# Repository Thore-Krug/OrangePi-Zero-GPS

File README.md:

# OrangePi-Zero-GPS
Addon Board for the OrangePi Zero Featuring a L80-R GPS Module

## Render

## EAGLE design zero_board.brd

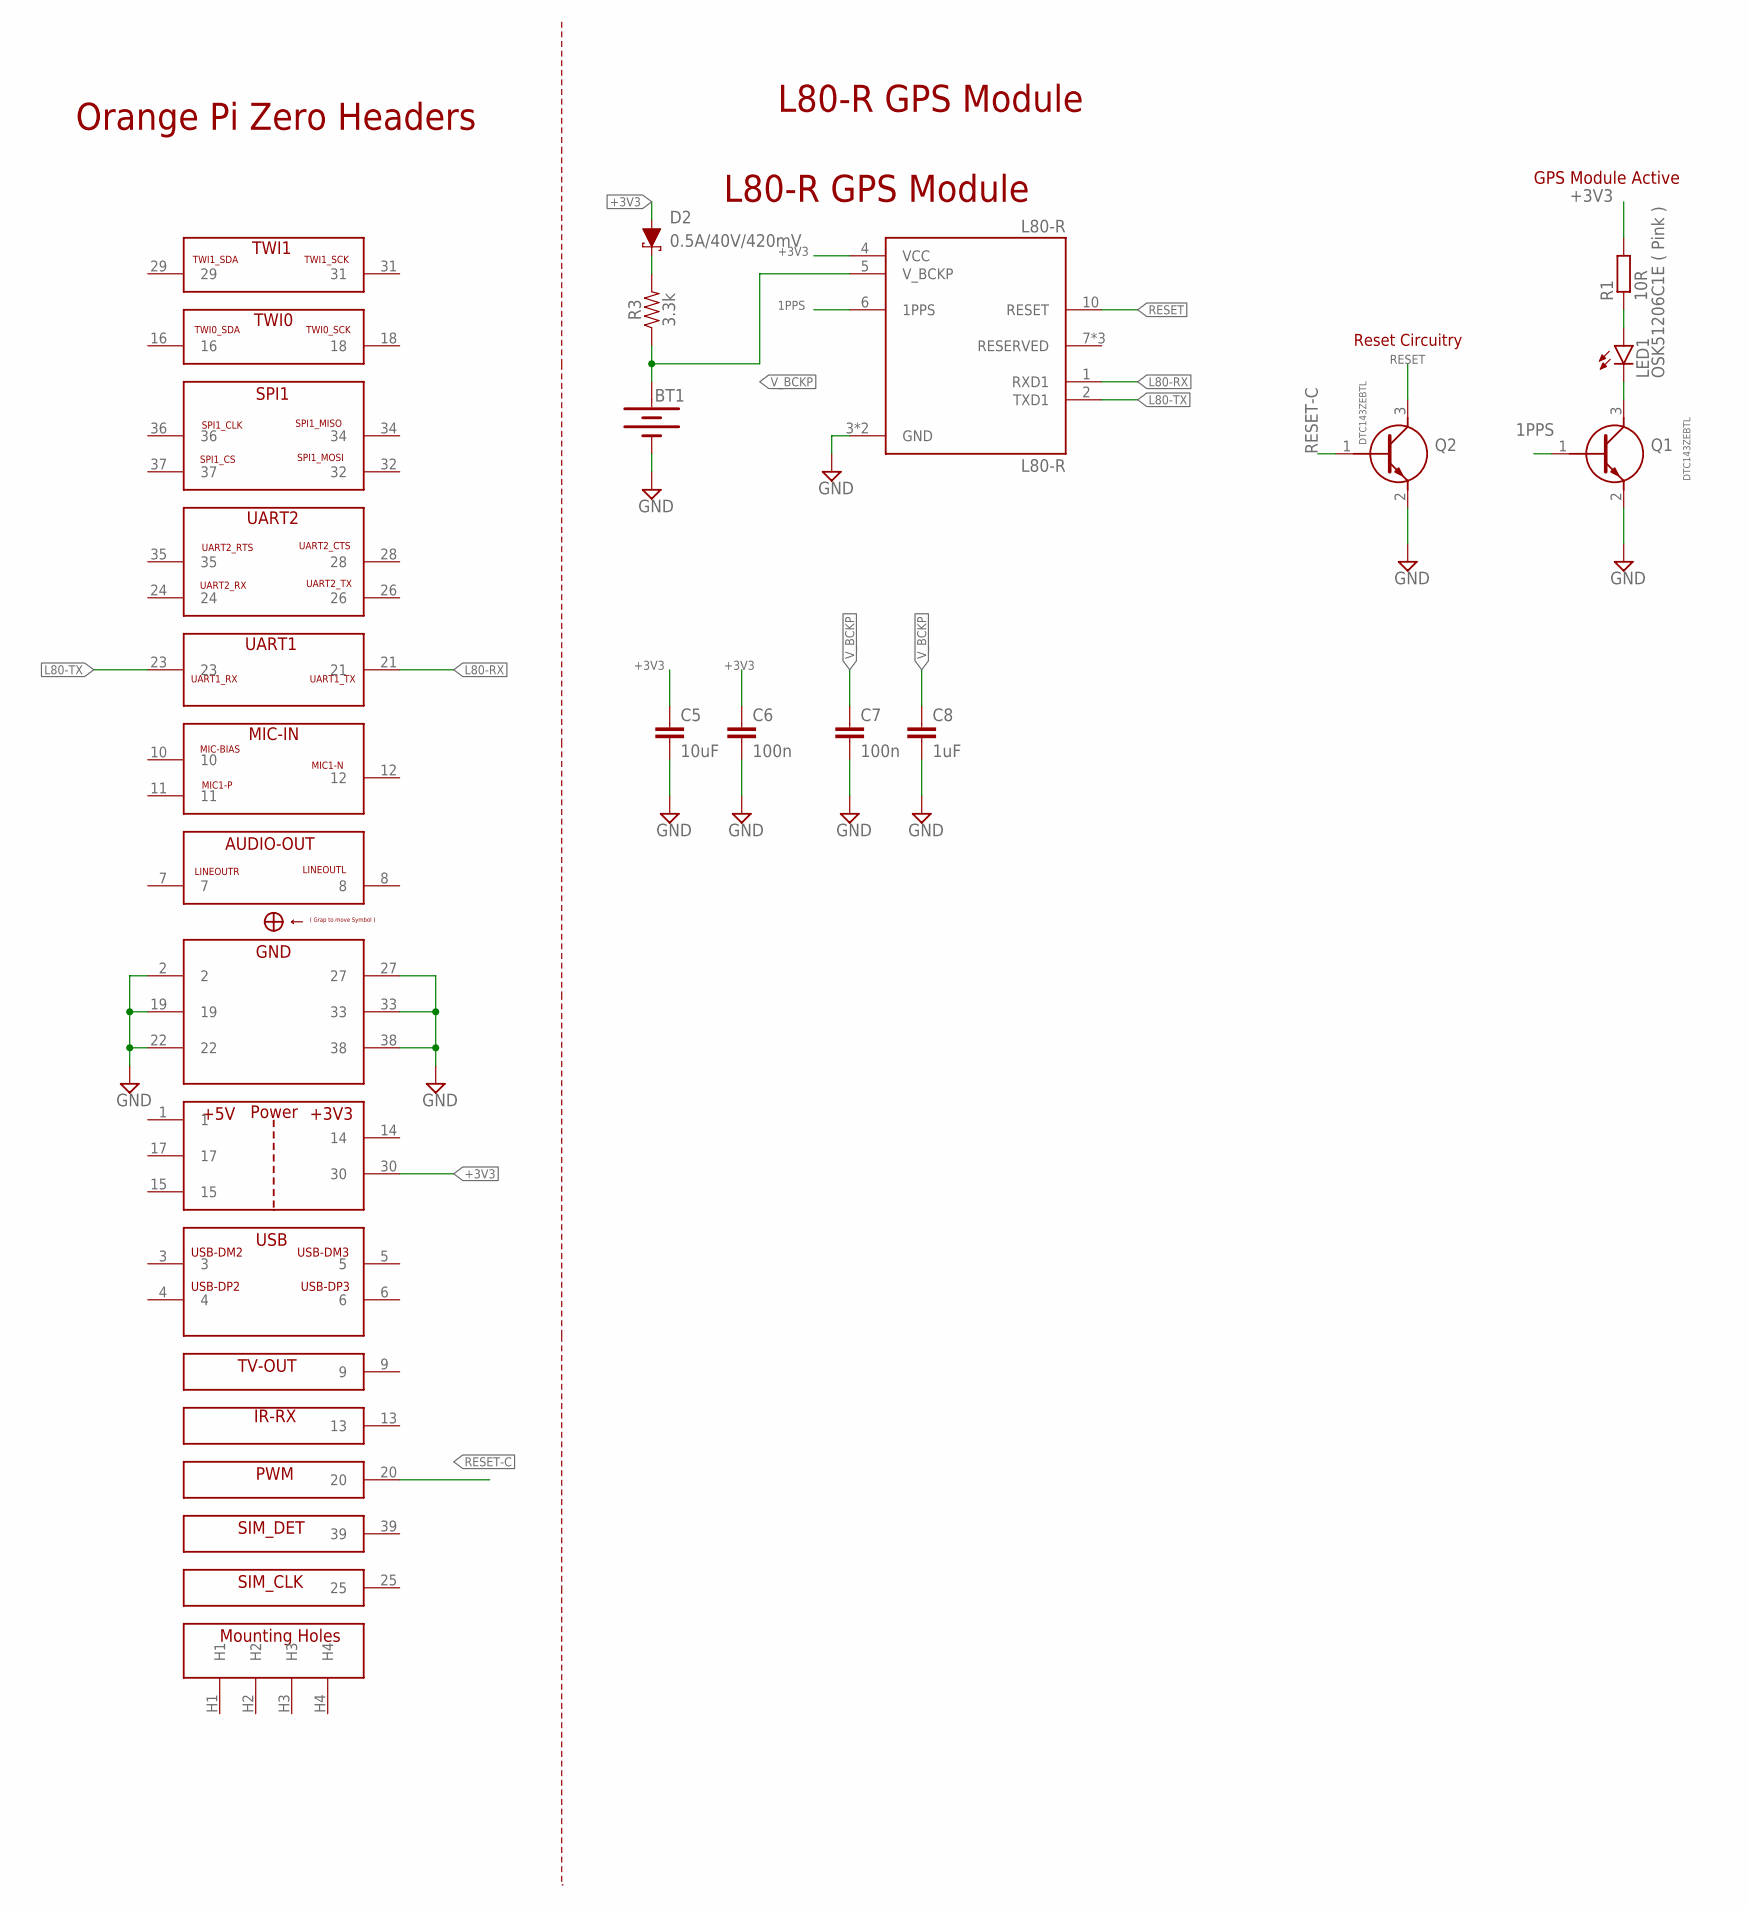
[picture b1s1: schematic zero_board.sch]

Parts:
BT1: 6.8MM_COIN_CELL; ML414H_IV01E
C5: 10uF; C0603
C6, C7: 100n; C0603
C8: 1uF; C0603
D2: 0.5A/40V/420mV; SOD-323
L80-R: L80-R; XCVR_L80-R
LED1: OSK51206C1E ( Pink ); CHIPLED_1206
Q1, Q2: DTC143ZEBTL; SOTFL50P160X85-3N
R1: 10R; R1206
R3: 3.3k; 0603
U$1: ORANGE-PI-ZERO-ADDON

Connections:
1: U$1.1
1PPS: L80-R.6 (1PPS), Q1.1 (B)
14: U$1.14
15: U$1.15
17: U$1.17
+3V3: C5.1, C6.1, D2.A, L80-R.4 (VCC), R1.2, U$1.30
GND: BT1.-, C5.2, C6.2, C7.2, C8.2, L80-R.3 (GND), L80-R.12 (GND), Q1.2 (E), Q2.2 (E), U$1.2, U$1.19, U$1.22, U$1.27, U$1.33, U$1.38
L80-RX: L80-R.1 (RXD1), U$1.21
L80-TX: L80-R.2 (TXD1), U$1.23
unnamed: LED1.C, Q1.3 (C)
unnamed: LED1.A, R1.1
unnamed: D2.C, R3.2
RESET: L80-R.10 (RESET), Q2.3 (C)
RESET-C: Q2.1 (B), U$1.20
V_BCKP: BT1.+, C7.1, C8.1, L80-R.5 (V_BCKP), R3.1

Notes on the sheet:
Orange Pi Zero Headers
L80-R GPS Module
Reset Circuitry
GPS Module Active

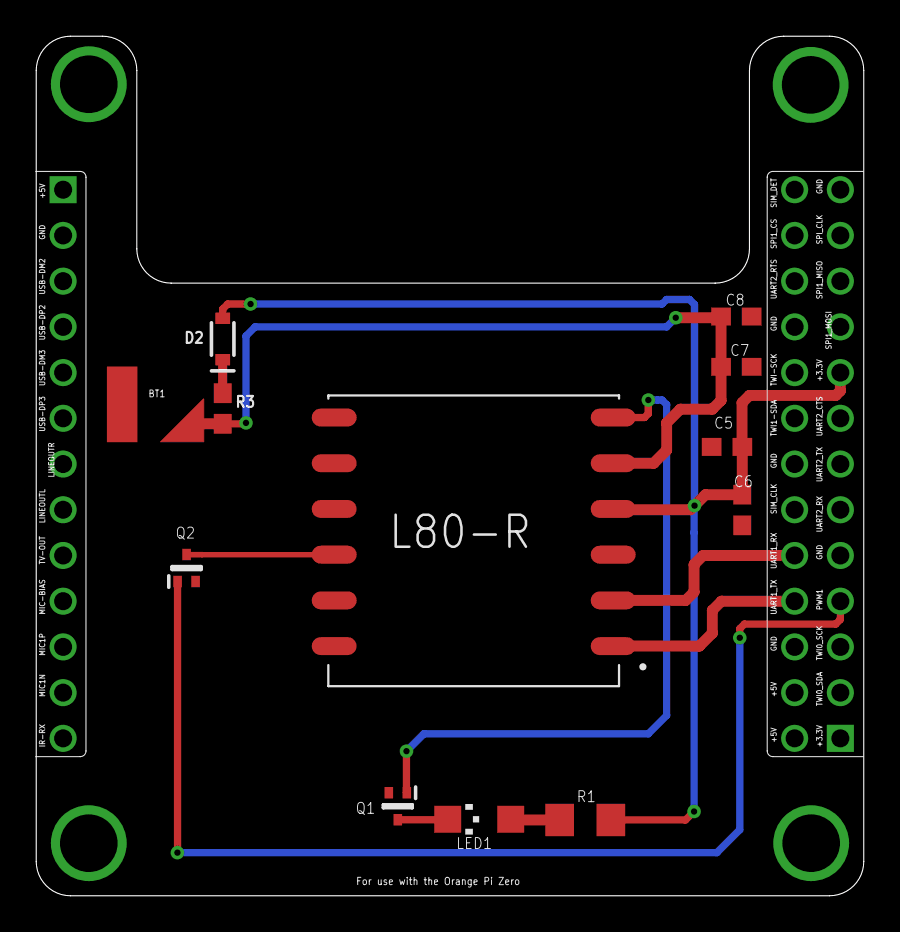
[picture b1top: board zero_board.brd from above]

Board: 2 copper layers, 46.0 x 47.8 mm, 13 parts (0 on the bottom side), 11 nets.

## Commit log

2020-11-25 Board Bringup
    Addition of Board Files, Datasheets, Image of Rendering.
    Signed off by: Thore Krug opensource[at]thorekrug.de
2020-11-25 Add Render of PCB
    Signed off by Thore Krug opensource[at]thorekrug.de

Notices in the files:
parts and their libraries:
SparkFun-Batteries: Licensing: Creative Commons ShareAlike 4.0 International - https://creativecommons.org/licenses/by-sa/4.0
